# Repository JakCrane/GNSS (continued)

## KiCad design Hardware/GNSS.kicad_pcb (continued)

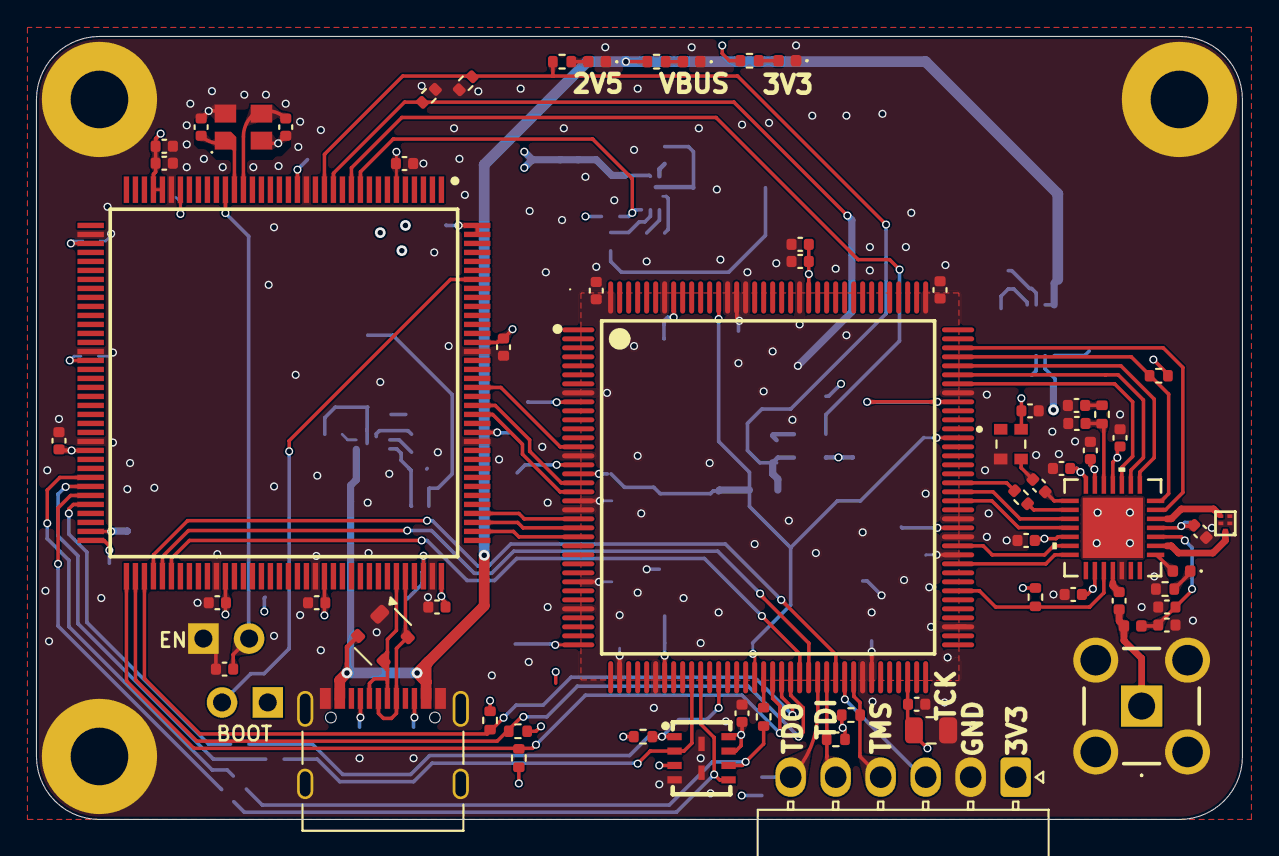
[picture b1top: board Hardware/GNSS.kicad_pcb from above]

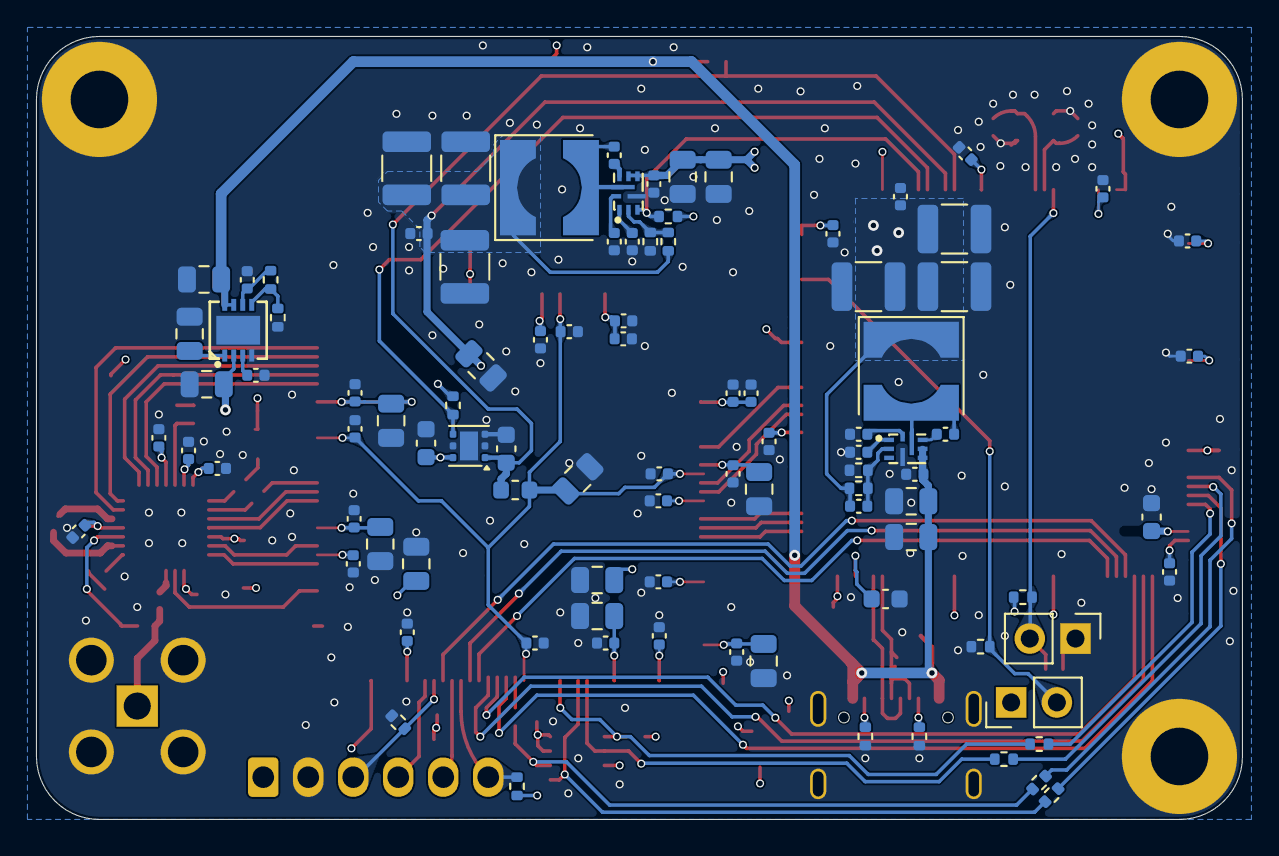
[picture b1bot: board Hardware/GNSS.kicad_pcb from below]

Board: 4 copper layers, 67.0 x 43.5 mm, 163 parts (96 on the bottom side), 84 nets.

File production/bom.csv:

Designator,Footprint,Quantity,Value,LCSC Part #
"C201, C202, C203, C204, C210, C213, C223, C401, C403, C409, C410, C411, C424, C429, C432, C433, C434",0805,17,10uF,
"C205, C207, C216, C217, C225, C228, C301, C302, C304, C306, C308, C309, C310, C311, C312, C313, C314, C316, C317, C320, C402, C404, C406, C407, C408, C412, C413, C414, C415, C416, C417, C418, C419, C420, C423, C425, C426, C427, C428, C430, C431, C501, C504, C507, C510, C513, C515, C516, C601",0402,49,100nF,
"C206, C209, C214, C221, C303, C318, C405, C421, C422",0402,9,1uF,
"C208, C215, C315, C319",0603,4,2.2uF,
"C211, C212, C512, C514",0402,4,10nF,
C218,0402,1,33pF,
"C219, C220, C222, C224, C226, C227",1210,6,22uF,
"C305, C307",0402,2,10pF,
"C502, C506, C508, C509, C517",0402,5,100pF,
"C503, C511",0402,2,470pF,
C505,0402,1,27pF,
"D201, D501",0402,2,RED_LED,
D202,0402,1,GREEN_LED,
D203,0402,1,WHITE_LED,
D701,SOT-143,1,SP0503BAHT,
FB401,0603,1,120Ω@100MHz,
IC301,QFP50P2200X2200X160-144N,1,STM32H743ZIT6TR,
J101,SMACONNECTOR,1,Conn_Coaxial,
J401,Molex_Nano-Fit_105313-xx06_1x06_P2.50mm_Horizontal,1,Conn_01x06_Pin,
J701,USB_C_Receptacle_Palconn_UTC16-G,1,USB_C_Receptacle_USB2.0,
"L201, L202",L_Wurth_WE-HEPA-5030,2,3.3uH,
L501,FILTER-SMD_5P-L1.1-W0.9-L_RSFP2413E,1,SAFFB1G56KB0F0AR1X,C91647
L502,0402,1,27nH,
"R201, R202, R301, R302, R303, R304, R501, R502, R601",0402,9,10kΩ,
R203,0402,1,16.7kΩ,
"R204, R206, R208, R503",0402,4,20kΩ,
R205,0402,1,33.2kΩ,
R207,0402,1,90.9kΩ,
R209,0402,1,330Ω,
R210,0402,1,200Ω,
"R211, R504",0402,2,1kΩ,
"R305, R306, R307, R308, R408",0402,5,22Ω,
"R401, R402, R403, R404, R405, R406, R407",0402,7,4.7kΩ,
R505,0402,1,0Ω,
"R701, R702",0402,2,5.1kΩ,
"U201, U202",VQFN-HR-9_2.0-W1.5-P0.5-TL_TI_RQF0009A,2,TPS566238RQFR,C5219353
U203,WSON-6-1EP_2x2mm_P0.65mm_EP1x1.6mm,1,TLV75525PDRV,
U204,LFCSP-8_L3.0-W3.0-P0.50-BL-EP,1,ADM7155ACPZ-04-R7,C209548
U301,CRYSTAL-SMD_4P-L3.2-W2.5-TR,1,ABM8G-25.000MHZ-B4Y-T,C596913
U401,TQFP-144_L20.0-W20.0-P0.50-LS22.0-TL,1,LFE5U-45F-6TG144C,C19979193
U501,21-0140_T2855&plus_3_MXM,1,MAX2769BETI/V+,
U601,USON-8_L4.0-W3.0-P0.80-BL_IS25WP032D,1,MX25L3233FZBI-08QTR,C2803002
Y501,OSC_TG2016SMN_25.0000M-ECGNNM3,1,TG2016SMN 16.3680M-MCGNNMB,

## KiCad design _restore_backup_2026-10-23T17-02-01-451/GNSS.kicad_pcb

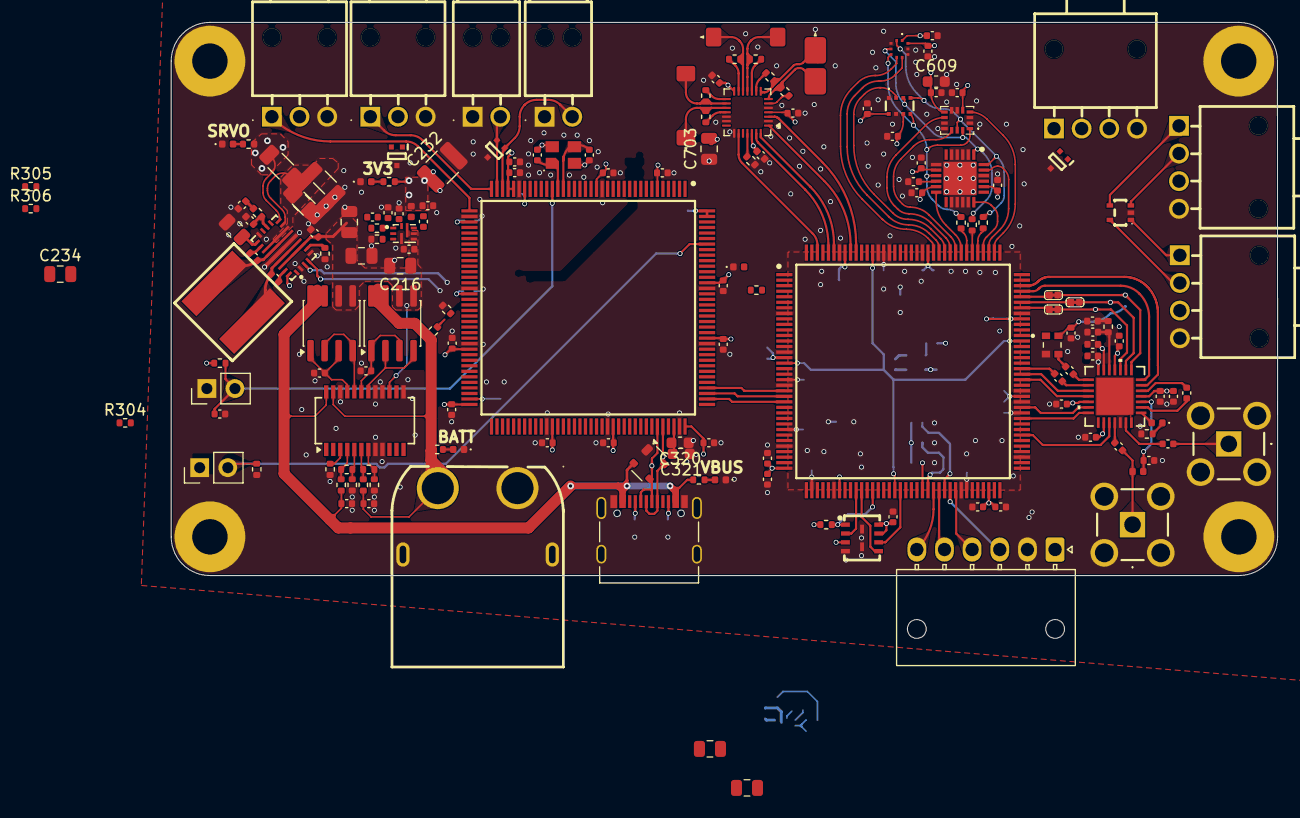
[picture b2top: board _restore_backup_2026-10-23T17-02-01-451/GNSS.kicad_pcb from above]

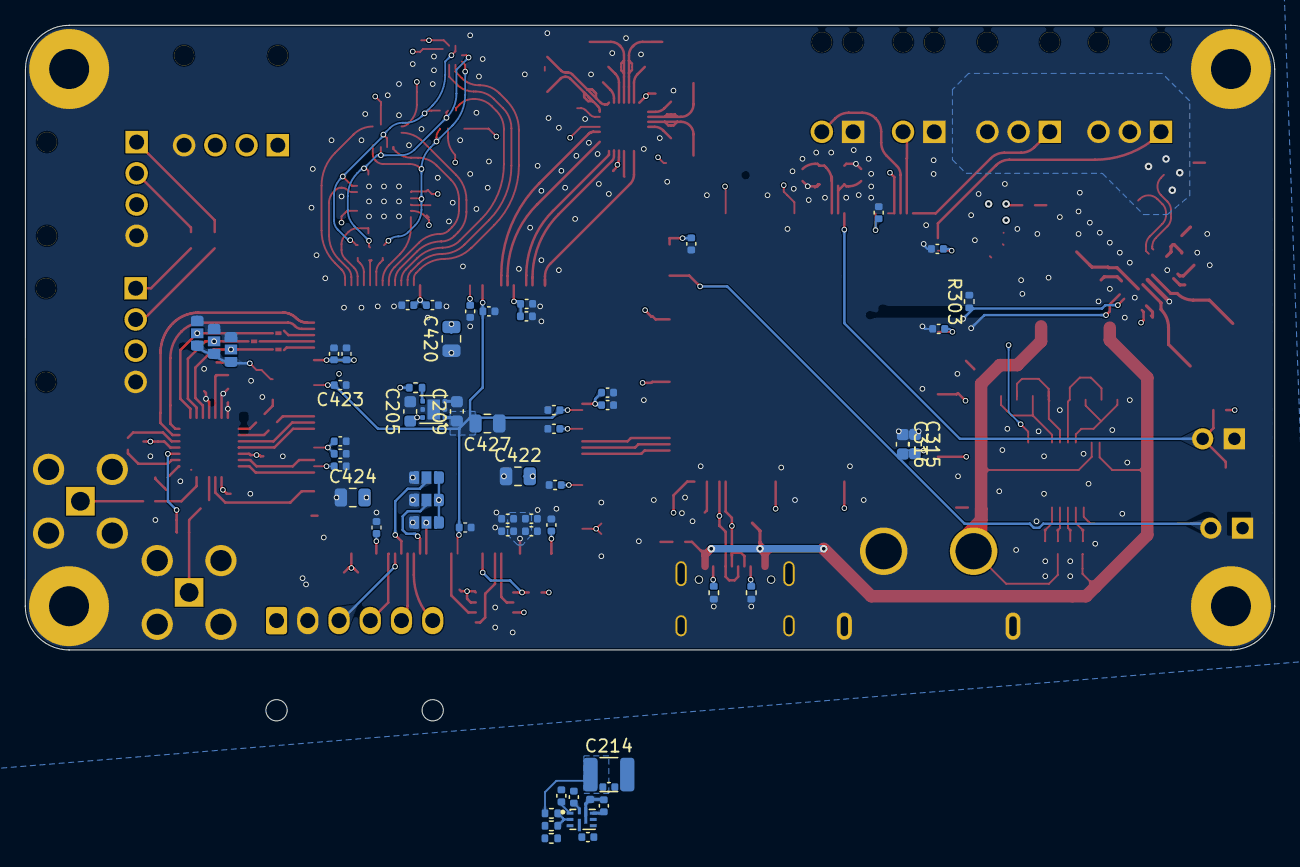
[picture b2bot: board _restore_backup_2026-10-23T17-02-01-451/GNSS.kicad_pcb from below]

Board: 4 copper layers, 100.0 x 50.0 mm, 227 parts (58 on the bottom side), 144 nets.

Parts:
C101, C207, C224, C509, C601, C605: 10nF; C_0402_1005Metric
C201, C210, C215, C218: 100nF 35V; C_0402_1005Metric
C202, C204, C208, C211, C217, C225, C226, C228, C233, C301, C304, C306, C307, C308, C309, C310, C311, C312, C313, C314, C317, C318, C322, C402, C403, C406, C408, C410, C412, C413, C415, C416, C419, C421, C423, C425, C426, C428, C430, C432, C434, C436, C502, C505, C506, C508, C513, C514, C515, C602, C603, C604, C606, C607, C608, C610, C611, C701, C702, C704, C801: 100nF; C_0402_1005Metric
C203, C230, C235, C236, C420, C422, C424, C427, C703: 10uF; C_0805_2012Metric
C205, C209, C315, C316, C320, C321, C609: 2.2uF; C_0603_1608Metric
C206, C223, C305, C319, C401, C404, C405, C407, C409, C411, C414, C417: 1uF; C_0402_1005Metric
C212, C213, C216, C234: 10uF 35V; C_0805_2012Metric
C214, C220, C221, C232: 22uF; C_1210_3225Metric
C227: 33pF; C_0402_1005Metric
C229: C_0402_1005Metric
C231: 2.2nF; C_0402_1005Metric
C302, C303: 10pF; C_0402_1005Metric
C418: 4.7uF; C_0402_1005Metric
C501: 100pF; C_0402_1005Metric
C503: 27pF; C_0402_1005Metric
C504, C507, C510, C511: 470pF; C_0402_1005Metric
C512: 23pF; C_0402_1005Metric
CN901: XT60PW-M; CONN-TH_XT60PW-M
CN902, CN903: 1053131202; CONN-TH_2P-P2.50_MOLEX_1053131202
CN904, CN905: 1053131203; CONN-TH_3P-P2.50_MOLEX_1053131203
CN906, CN907, CN908: 1053131204; CONN-TH_4P-P2.50_MOLEX_1053131204
D201, D501: RED_LED; LED_0402_1005Metric
D202: GREEN_LED; LED_0402_1005Metric
D203: WHITE_LED; LED_0402_1005Metric
D204: BLUE_LED; LED_0402_1005Metric
D205: YELLOW_LED; LED_0402_1005Metric
D901: SP0503BAHT; SOT-143
D902: PESD3V3L4UG,115; SOT-353_L2.0-W1.2-P0.65-LS2.1-TL
D903, D904, D905: PESD3V3S2UQ,115; SOTFL50P160X60-3N
H101, H102, H103, H104: MountingHole_Pad; MountingHole_3.2mm_M3_Pad
IC301: STM32H743ZIT6TR; QFP50P2200X2200X160-144N
IC601: IIM-20670; QFN50P450X450X115-25N
IC602: DPS368XTSA1
IC603: ICM-42688-P; IIM42352
IC604: BMP390
J101, J102: Conn_Coaxial; SMACONNECTOR
J401: Conn_01x06_Pin; Molex_Nano-Fit_105313-xx06_1x06_P2.50mm_Horizontal
J901: USB_C_Receptacle_USB2.0; USB_C_Receptacle_Palconn_UTC16-G
JP401, JP402, JP403, JP504, JP505, JP506: SolderJumper_3_Open; small_3pin_SolderJP
JP501, JP502, JP503: SolderJumper_2_Bridged; small_2_pad_jumper_closed
L201: 1uH; L_0402_1005Metric
L202: 2.7uH; L_0402_1005Metric
L203: 4.7uH; IND-SMD_L7.5-W7.2-1
L501: 27nH; L_0402_1005Metric
Q201, Q202: IRF7324; SOIC-8_3.9x4.9mm_P1.27mm
R201, R202, R203, R205, R401, R402, R403, R501, R502: 1kΩ; R_0402_1005Metric
R204, R219, R222, R223, R301, R302, R303, R304, R305, R306, R802: 10kΩ; R_0402_1005Metric
R206: 1.05MΩ; R_0402_1005Metric
R207: 31.6kΩ; R_0402_1005Metric
R208: 68.1kΩ; R_0402_1005Metric
R209: 402kΩ; R_0402_1005Metric
R210: 21.8kΩ; R_0402_1005Metric
R211: 93.1kΩ; R_0402_1005Metric
R212, R220, R221: 255kΩ; R_0402_1005Metric
R213: 16.7kΩ; R_0402_1005Metric
R214, R218: 20kΩ; R_0402_1005Metric
R215: 49.9kΩ; R_0402_1005Metric
R216: 10mΩ; R_1206_3216Metric
R217: 90.9kΩ; R_0402_1005Metric
R701: 33kΩ; R_0402_1005Metric
R702, R703, R704, R705, R706, R707: 121Ω; R_0402_1005Metric
R708: Sen-x; RM3100-xy
R709: Sen-y; RM3100-xy
R710: Sen-z; RM3100-z
R901, R902: 5.1kΩ; R_0402_1005Metric
SW301, SW302: SW_Push; PinHeader_1x02_P2.54mm_Vertical
U201: LTC4417IGN; SSOP-24_3.9x8.7mm_P0.635mm
U202, U204: TPS566238RQFR; VQFN-HR-9_2.0-W1.5-P0.5-TL_TI_RQF0009A
U203: TLV75525PDRV; WSON-6-1EP_2x2mm_P0.65mm_EP1x1.6mm
U205: TPS55289RYQR; VQFN-21_L5.0-W3.0-P0.50-TL
U301: ABM8G-25.000MHZ-B4Y-T; CRYSTAL-SMD_4P-L3.2-W2.5-TR
U401: LFE5U-45F-6TG144C; QFP50P2200X2200X160-144N
U501: MAX2769BETI/V+; 21-0140_T2855&plus_3_MXM
U701: RM3100
U802: MX25L3233FZBI-08QTR; USON-8_L4.0-W3.0-P0.80-BL_IS25WP032D
Y101: TG2016SMN 16.3680M-MCGNNMB; OSC_TG2016SMN_25.0000M-ECGNNM3

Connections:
+1V1: C214.1, C217.1, C420.2, C422.2, C424.2, C426.2, C428.2, C430.2, C432.2, C434.2, C436.2, IC301.26 (PC0), L201.2, R213.2, R305.1, U401.20 (VCC), U401.29 (VCC), U401.38 (VCC), U401.66 (VCC), U401.83 (VCC), U401.130 (VCC)
+2V5: C209.1, C419.2, C421.2, C423.2, C425.2, C427.2, IC301.28 (PC2_C), R201.2, R306.1, U203.1 (OUT), U401.17 (VCCAUX), U401.53 (VCCAUX), U401.96 (VCCAUX), U401.132 (VCCAUX)
+3V3: C101.1, C204.1, C205.1, C227.1, C232.1, C233.1, C235.1, C236.1, C304.2, C305.2, C306.2, C307.2, C308.2, C309.1, C310.2, C311.1, C312.2, C313.2, C314.1, C317.2, C318.2, C319.2, C322.2, C401.2, C402.2, C403.2, C404.2, C405.2, C406.2, C407.2, C408.2, C409.2, C410.2, C411.2, C412.2, C413.2, C414.2, C415.2, C416.2, C417.2, C418.2, C501.2, C502.2, C505.2, C506.1, C508.1, C513.2, C514.2, C601.1, C603.1, C604.1, C605.1, C606.1, C607.1, C608.1, C609.1, C610.2, C611.1, C701.1, C702.1, C703.2, C704.1, C801.1, CN906.3, CN907.3, CN908.3, IC301.6 (VBAT), IC301.17 (VDD_1), IC301.30 (VDD_2), IC301.32 (VREF+), IC301.33 (VDDA), IC301.39 (VDD_3), IC301.52 (VDD_4), IC301.62 (VDD_5), IC301.72 (VDD_6), IC301.84 (VDD_7), IC301.95 (VDD33USB), IC301.108 (VDD_8), IC301.121 (VDD_9), IC301.131 (VDD_10), IC301.143 (PDR_ON), IC301.144 (VDD_11), IC601.8 (VDDIO), IC601.11 (VDD), IC601.20 (VPP), IC602.6 (VDDIO), IC602.8 (VDD), IC603.5 (VDDIO), IC603.8 (VDD), IC604.1 (VDDIO), IC604.10 (VDD), J401.1, JP401.3 (B), JP402.3 (B), JP403.3 (B), JP504.3 (B), JP505.3 (B), JP506.3 (B), L202.2, R202.2, R217.2, R222.2, R223.2, R302.2, R303.2, R304.2, R802.2, SW301.1, U202.5 (VIN), U202.6 (VIN), U203.6 (IN), U205.21 (EXTVCC), U401.16 (VCCIO6), U401.36 (VCCIO6), U401.43 (VCCIO8), U401.70 (VCCIO3), U401.86 (VCCIO3), U401.100 (VCCIO2), U401.122 (VCCIO1), U401.137 (VCCIO0), U501.4 (VCC_RF), U501.11 (VCC_VCO), U501.13 (VCC_CP), U501.14 (VCCD), U501.19 (VCC_ADC), U501.23 (VCC_IF), U701.4 (AVDD), U701.14 (DVDD), U701.26 (DVDD), U802.3 (~WP/SIO2), U802.7 (~HOLD/SIO3), U802.8 (VCC), Y101.4 (VCC)
/Connectors/Data+: D901.4 (K), IC301.104 (PA12), J901.A6 (D+), J901.B6 (D+)
/Connectors/Data-: D901.3 (K), IC301.103 (PA11), J901.A7 (D-), J901.B7 (D-)
/Connectors/ESC_PWM_0: CN902.2, D903.1 (A), IC301.34 (PA0)
/Connectors/ESC_PWM_1: CN903.2, D903.2 (B), IC301.35 (PA1)
/Connectors/SCL_0: CN906.2, CN907.2, D902.3 (B), D902.5 (D), IC301.11 (PF1)
/Connectors/SDA_0: CN906.1, CN907.1, D902.1 (A), D902.4 (C), IC301.10 (PF0)
/Connectors/SERVO_PWM_0: CN905.1, D905.1 (A), IC301.36 (PA2)
/Connectors/SERVO_PWM_1: CN904.1, D905.2 (B), IC301.37 (PA3)
/Connectors/SERVO_PWR: CN904.2, CN905.2, R205.2, R216.2, U205.13 (ISN)
/Connectors/UART_RX: CN908.2, D904.1 (A), IC301.135 (PB5)
/Connectors/UART_TX: CN908.1, D904.2 (B), IC301.134 (PB4)
/Connectors/VBUS: C202.2, D901.2 (K), J901.A4 (VBUS), J901.A9 (VBUS), J901.B4 (VBUS), J901.B9 (VBUS), Q201.7 (D1), Q201.8 (D1), R203.2, R209.2, U201.24 (V1)
/FPGA/BARO_0_DRDY: IC604.7 (INT), U401.120 (PT53A)
/FPGA/CLKOUT: C509.2, U401.91 (PR23A)
/FPGA/FPGA_FLASH_SPI.CS: R802.1, U401.49 (PB15A), U802.1 (~CS)
/FPGA/FPGA_FLASH_SPI.MISO: U401.46 (PB11A), U802.2 (SO/SIO1)
/FPGA/FPGA_FLASH_SPI.MOSI: U401.47 (PB11B), U802.5 (SI/SIO0)
/FPGA/FPGA_FLASH_SPI.SCK: U401.54 (CCLK), U802.6 (SCLK)
/FPGA/FPGA_IRQ: IC301.111 (PC10), U401.23 (PL35D)
/FPGA/FPGA_RESET: IC301.112 (PC11), U401.22 (PL35C)
/FPGA/I0: U401.84 (PR32C), U501.20 (I0)
/FPGA/I1: U401.82 (PR32D), U501.21 (I1)
/FPGA/IDLE: U401.79 (PR35B), U501.24 (*IDLE)
/FPGA/IMU_0_ODR: IC601.12 (ODR), U401.116 (PT58A)
/FPGA/IMU_0_RESET: IC601.18 (RESETN), U401.112 (PT62A)
/FPGA/IMU_1_CLKIN: IC603.9 (INT2_/_FSYNC_/_CLKIN), U401.118 (PT56A)
/FPGA/IMU_1_DRDY: IC603.4 (INT1_/_INT), U401.110 (PT67A)
/FPGA/LD: U401.106 (PR2D), U501.6 (LD)
/FPGA/MAG_CS: U401.135 (PT13B), U701.3 (SSN)
/FPGA/MAG_DRDY: U401.142 (PT4B), U701.23 (DRDY)
/FPGA/MCU_SPI_CS: IC301.110 (PA15), U401.24 (PL38A)
/FPGA/MCU_SPI_MISO: IC301.124 (PG9), U401.18 (PL32B)
/FPGA/MCU_SPI_MOSI: IC301.123 (PD7), U401.19 (PL35B)
/FPGA/MCU_SPI_SCK: IC301.126 (PG11), U401.14 (PL23D)
/FPGA/Q0: U401.89 (PR23B), U501.18 (Q0)
/FPGA/Q1: U401.90 (PR23C), U501.17 (Q1)
/FPGA/RF_SPI_CS: JP503.1 (A), U401.102 (PR8D)
/FPGA/RF_SPI_MOSI: JP501.1 (A), U401.104 (PR8C)
/FPGA/RF_SPI_SCLK: JP502.1 (A), U401.103 (PR8B)
/FPGA/SEN_0_SPI_CS_0: IC601.23 (NCS), U401.111 (PT62B)
/FPGA/SEN_0_SPI_CS_1: IC603.12 (AP_CS), U401.117 (PT56B)
/FPGA/SEN_0_SPI_CS_2: IC604.6 (CSB), U401.121 (PT51A)
/FPGA/SEN_0_SPI_CS_3: IC602.2 (CSB), U401.119 (PT53B)
/FPGA/SEN_0_SPI_MISO: IC601.9 (MISO), IC602.5 (SDO), IC603.1 (AP_SDO_/_AP_AD0), IC604.5 (SDO), R401.2
/FPGA/SEN_0_SPI_MOSI: IC601.1 (MOSI), IC602.3 (SDI), IC603.14 (AP_SDA_/_AP_SDIO_/_AP_SDI), IC604.4 (SDI), R402.2
/FPGA/SEN_0_SPI_SCK: IC601.24 (SCLK), IC602.4 (SCK), IC603.13 (AP_SCL_/_AP_SCLK), IC604.2 (SCK), R403.2
/FPGA/SEN_1_SPI_MISO: U401.139 (PT9B), U701.28 (MISO)
/FPGA/SEN_1_SPI_MOSI: U401.136 (PT13A), U701.1 (MOSI)
/FPGA/SEN_1_SPI_SCLK: U401.140 (PT9A), U701.27 (SCLK)
/FPGA/SHDN: U401.105 (PR8A), U501.7 (*SHDN)
/FPGA/TCXO: C512.2, Y101.3 (OUT)
/MCU/1v1_enable: IC301.27 (PC1), R223.1, U202.3 (EN)
/MCU/2v5_enable: IC301.29 (PC3_C), R222.1, U203.4 (EN)
/MCU/BOOT: IC301.138 (BOOT0), R301.2, SW301.2
/MCU/Batt_Volt_Monitor: IC301.42 (PA6), R220.1, R221.2
/MCU/NRST: C301.1, IC301.25 (NRST), R302.1, SW302.2
/MCU/SCL_PWR: IC301.54 (PF14), R303.1, U205.3 (SCL)
/MCU/SDA_PWR: IC301.55 (PF15), R304.1, U205.4 (SDA)
/MCU/SERVO_PWR_FAULT: IC301.41 (PA5), U205.14 (FB/~INT)
/Power/BATT: C201.1, CN901.2 (+), Q202.7 (D1), Q202.8 (D1), R204.2, R206.2, R220.2, U201.23 (V2)
/Power/SW1: C226.1, L203.1, U205.8 (SW1)
/Power/SW2: C228.1, L203.2, U205.10 (SW2)
/Power/VOUT_pre_shunt: C203.1, C220.2, C221.2, R216.1, U205.11 (VOUT), U205.12 (ISP)
/RF Frontend/ANTBIAS: C515.1, L501.1, U501.3 (ANTBIAS)
/RF Frontend/ANT_LED: D501.2 (A), U501.1 (ANTFLAG)
/RF Frontend/Active_Antenna: C511.2, J102.1, L501.2
/RF Frontend/CS: JP503.2 (B), JP506.2 (C), U501.10 (*CS)
/RF Frontend/Passive_Antenna: C510.2, J101.1
/RF Frontend/SCLK: JP502.2 (B), JP505.2 (C), U501.9 (SCLK)
/RF Frontend/SDATA: JP501.2 (B), JP504.2 (C), U501.8 (SDATA)
GND: C101.2, C201.2, C202.1, C203.2, C204.2, C205.2, C206.2, C207.2, C208.1, C209.2, C210.2, C212.2, C213.2, C214.2, C215.2, C216.2, C217.2, C218.2, C220.1, C221.1, C223.2, C224.2, C229.2, C230.2, C231.2, C232.2, C233.2, C234.2, C235.2, C236.2, C301.2, C302.1, C303.2, C304.1, C305.1, C306.1, C307.1, C308.1, C309.2, C310.1, C311.2, C312.1, C313.1, C314.2, C315.1, C316.1, C317.1, C318.1, C319.1, C320.1, C321.1, C322.1, C401.1, C402.1, C403.1, C404.1, C405.1, C406.1, C407.1, C408.1, C409.1, C410.1, C411.1, C412.1, C413.1, C414.1, C415.1, C416.1, C417.1, C418.1, C419.1, C420.1, C421.1, C422.1, C423.1, C424.1, C425.1, C426.1, C427.1, C428.1, C430.1, C432.1, C434.1, C436.1, C501.1, C502.1, C503.2, C504.2, C505.1, C506.2, C508.2, C513.1, C514.1, C515.2, C601.2, C602.2, C603.2, C604.2, C605.2, C606.2, C607.2, C608.2, C609.2, C610.1, C611.2, C701.2, C702.2, C703.1, C704.2, C801.2, CN901.1 (-), CN901.3, CN901.4, CN902.1, CN903.1, CN904.3, CN905.3, CN906.4, CN907.4, CN908.4, D201.1 (K), D202.1 (K), D203.1 (K), D204.1 (K), D205.1 (K), D901.1 (A), D902.2 (GND), D903.3 (GND), D904.3 (GND), D905.3 (GND), H101.1 (1_1), H102.1 (1_1), H103.1 (1_1), H104.1 (1_1), IC301.16 (VSS_1), IC301.31 (VSSA), IC301.38 (VSS_2), IC301.51 (VSS_3), IC301.61 (VSS_4), IC301.83 (VSS_5), IC301.94 (VSS_6), IC301.107 (VSS_7), IC301.120 (VSS_8), IC301.130 (VSS_9), IC601.2 (GND_1), IC601.3 (GND_2), IC601.4 (GND_3), IC601.5 (GND_4), IC601.7 (GND_5), IC601.14 (GND_6), IC601.15 (GND_7), IC601.16 (GND_8), IC601.17 (GND_9), IC601.22 (GND_10), IC601.25 (THERMAL_PAD), IC602.1 (GND_1), IC602.7 (GND_2), IC603.2 (RESV_1), IC603.3 (RESV_2), IC603.6 (GND), IC603.7 (RESV_3), IC603.10 (RESV_4), IC603.11 (RESV_5), IC604.3 (VSS_1), IC604.8 (VSS_2), IC604.9 (VSS_3), J101.2, J101.3, J101.4, J101.5, J102.2, J102.3, J102.4, J102.5, J401.2, J901.A1 (GND), J901.A12 (GND), J901.B1 (GND), J901.B12 (GND), J901.S1 (SHIELD), JP401.1 (A), JP402.1 (A), JP403.1 (A), JP504.1 (A), JP505.1 (A), JP506.1 (A), R208.1, R211.1, R212.1, R214.1, R215.2, R218.1, R221.1, R301.1, R305.2, R306.2, R502.1, R701.1, R901.2, R902.1, SW302.1, U201.8 (UV3), U201.9 (OV3), U201.13 (GND), U201.16 (G3), U201.17 (VS3), U201.22 (V3), U202.4 (PGND), U203.2 (NC), U203.3 (GND), U203.5 (NC), U203.7 (GND), U204.4 (PGND), U205.2 (MODE), U205.5 (DITH/SYNC), U205.9 (PGND), U205.17 (AGND), U301.2, U301.4, U401.8 (GND), U401.15 (GND), U401.21 (GND), U401.32 (VSSIO6), U401.42 (GND), U401.65 (GND), U401.75 (GND), U401.85 (GND), U401.87 (GND), U401.101 (GND), U401.123 (GND), U401.129 (GND), U401.131 (GND), U401.138 (GND), U501.26 (PGM), U501.29 (EP), U701.2 (RES), U701.5 (AVSS), U701.19 (DVSS), U701.20 (RES), U701.22 (I2C), U802.4 (GND), U802.9 (EP), U802.10 (EP), Y101.2 (GND)
unnamed: C231.1, R219.2
unnamed: C504.1, R501.2
unnamed: D201.2 (A), R201.1
unnamed: D202.2 (A), R202.1
unnamed: D203.2 (A), R203.1
unnamed: D204.2 (A), R204.1
unnamed: D205.2 (A), R205.1
unnamed: D501.1 (K), R502.2
unnamed: C303.1, IC301.23 (PH0-OSC_IN), U301.3 (OSC2)
unnamed: C302.2, IC301.24 (PH1-OSC_OUT), U301.1 (OSC1)
unnamed: C315.2, C316.2, IC301.71 (VCAP_1)
unnamed: C320.2, C321.2, IC301.106 (VCAP_2)
unnamed: C602.1, IC601.10 (REGOUT)
unnamed: J401.3, U401.63 (TCK)
unnamed: J401.4, U401.64 (TMS)
unnamed: J401.5, U401.61 (TDI)
unnamed: J401.6, U401.60 (TDO)
unnamed: J901.A5 (CC1), R901.1
unnamed: J901.B5 (CC2), R902.2
unnamed: JP401.2 (C), U401.59 (CFG_1)
unnamed: JP402.2 (C), U401.62 (CFG_0)
unnamed: JP403.2 (C), U401.58 (CFG_2)
unnamed: Q201.2 (G1), Q201.4 (G2), U201.20 (G1)
unnamed: C208.2, Q201.1 (S1), Q201.3 (S2), U201.21 (VS1)
unnamed: Q202.2 (G1), Q202.4 (G2), U201.18 (G2)
unnamed: C210.1, Q202.1 (S1), Q202.3 (S2), U201.19 (VS2)
unnamed: R212.2, U201.3 (HYS)
unnamed: R210.1, R211.2, U201.5 (OV1)
unnamed: R207.1, R208.2, U201.7 (OV2)
unnamed: R209.1, R210.2, U201.4 (UV1)
unnamed: R206.1, R207.2, U201.6 (UV2)
unnamed: C212.1, C213.1, C215.1, C216.1, C218.1, C234.1, Q201.5 (D2), Q201.6 (D2), Q202.5 (D2), Q202.6 (D2), U201.15 (VOUT), U204.5 (VIN), U204.6 (VIN), U205.7 (VIN)
unnamed: C211.1, U202.7 (BST)
unnamed: R213.1, R214.2, U202.2 (FB)
unnamed: C207.1, U202.9 (SS)
unnamed: C211.2, L201.1, U202.8 (SW)
unnamed: C206.1, U202.1 (VCC)
unnamed: C225.1, U204.7 (BST)
unnamed: C227.2, R217.1, R218.2, U204.2 (FB)
unnamed: C224.1, U204.9 (SS)
unnamed: C225.2, L202.1, U204.8 (SW)
unnamed: C223.1, U204.1 (VCC)
unnamed: C226.2, U205.20 (BOOT1)
unnamed: C228.2, U205.19 (BOOT2)
unnamed: C229.1, R219.1, U205.15 (COMP)
unnamed: R215.1, U205.6 (FSW)
unnamed: C230.1, U205.18 (VCC)
unnamed: R401.1, U401.115 (PT58B)
unnamed: R402.1, U401.114 (PT60A)
unnamed: R403.1, U401.113 (PT60B)
unnamed: C509.1, U501.16 (CLKOUT)
unnamed: C503.1, R501.1, U501.12 (CPOUT)
unnamed: C510.1, U501.27 (LNA1)
unnamed: C511.1, U501.25 (LNA2)
unnamed: C507.1, U501.2 (LNAOUT)
unnamed: C507.2, U501.5 (MIXIN)
unnamed: C512.1, U501.15 (XTAL)
unnamed: R701.2, U701.25 (REXT)
unnamed: R702.1, U701.18 (XDRVN)
unnamed: R705.1, U701.15 (XDRVP)
unnamed: R702.2, R708.2, U701.17 (XINN)
unnamed: R705.2, R708.1, U701.16 (XINP)
unnamed: R703.1, U701.13 (YDRVN)
unnamed: R706.1, U701.10 (YDRVP)
unnamed: R703.2, R709.2, U701.12 (YINN)
unnamed: R706.2, R709.1, U701.11 (YINP)
unnamed: R704.1, U701.9 (ZDRVN)
unnamed: R707.1, U701.6 (ZDRVP)
unnamed: R704.2, R710.2, U701.8 (ZINN)
unnamed: R707.2, R710.1, U701.7 (ZINP)

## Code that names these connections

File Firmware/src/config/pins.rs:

//! Every MCU pin and peripheral the board uses, in one place.
//!
//! This is the only file that names physical pins (PA12, PE15, ...). Each
//! subsystem gets its own struct, and `Board::new` hands each pin to exactly
//! one owner, so two modules can't accidentally drive the same pin.
//!
//! Taking a pin here does not configure it: it stays in its reset state
//! (analog, no pull) until a module actually sets it up.

use embassy_stm32::peripherals::*;
use embassy_stm32::{Peri, Peripherals};

/// USB full-speed, J701.
pub struct UsbPins {
    pub otg: Peri<'static, USB_OTG_FS>,
    pub dp: Peri<'static, PA12>, // D+
    pub dm: Peri<'static, PA11>, // D-
}

/// MX25L3233F NOR flash, U601 (shared with the FPGA's config pins).
pub struct FlashPins {
    pub spi: Peri<'static, SPI4>,
    pub sck: Peri<'static, PE12>,  // via R305
    pub miso: Peri<'static, PE13>, // via R306
    pub mosi: Peri<'static, PE14>, // via R307
    pub cs: Peri<'static, PE15>,   // via R308, 10k pull-up R601
}

/// ECP5 FPGA, U401.
pub struct FpgaPins {
    // Configuration / status
    pub programn: Peri<'static, PB13>, // 4.7k pull-up R401
    pub initn: Peri<'static, PB12>,    // 4.7k pull-up R402
    pub done: Peri<'static, PB14>,     // 4.7k pull-up R403
    pub cfg0: Peri<'static, PB15>,
    pub cfg1: Peri<'static, PD8>,
    pub cfg2: Peri<'static, PD9>,
    // User I/O
    pub reset: Peri<'static, PC11>,
    pub irq: Peri<'static, PC10>,
    // MCU <-> FPGA SPI bus (SPI1)
    pub spi: Peri<'static, SPI1>,
    pub sck: Peri<'static, PG11>,
    pub miso: Peri<'static, PG9>,
    pub mosi: Peri<'static, PD7>,
    pub cs: Peri<'static, PA15>,
}

/// FPGA rail enables and voltage sense.
pub struct PowerPins {
    pub en_1v1: Peri<'static, PF0>,    // U202 EN, 10k pull-up R201
    pub en_2v5: Peri<'static, PF1>,    // U203 EN, 10k pull-up R202
    pub sense_1v1: Peri<'static, PF3>, // ADC3_INP5
    pub sense_2v5: Peri<'static, PF4>, // ADC3_INP9
}

/// Everything, grouped by subsystem.
pub struct Board {
    pub usb: UsbPins,
    pub flash: FlashPins,
    pub fpga: FpgaPins,
    pub power: PowerPins,
    pub adc3: Peri<'static, ADC3>, // die temperature, VREFINT, rail sense
}

impl Board {
    /// Split the chip's peripherals into the board's subsystems.
    pub fn new(p: Peripherals) -> Self {
        Board {
            usb: UsbPins { otg: p.USB_OTG_FS, dp: p.PA12, dm: p.PA11 },
            flash: FlashPins { spi: p.SPI4, sck: p.PE12, miso: p.PE13, mosi: p.PE14, cs: p.PE15 },
            fpga: FpgaPins {
                programn: p.PB13,
                initn: p.PB12,
                done: p.PB14,
                cfg0: p.PB15,
                cfg1: p.PD8,
                cfg2: p.PD9,
                reset: p.PC11,
                irq: p.PC10,
                spi: p.SPI1,
                sck: p.PG11,
                miso: p.PG9,
                mosi: p.PD7,
                cs: p.PA15,
            },
            power: PowerPins { en_1v1: p.PF0, en_2v5: p.PF1, sense_1v1: p.PF3, sense_2v5: p.PF4 },
            adc3: p.ADC3,
        }
    }
}
